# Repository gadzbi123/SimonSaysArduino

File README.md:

# SimonSaysArduino
Simple Arduino project

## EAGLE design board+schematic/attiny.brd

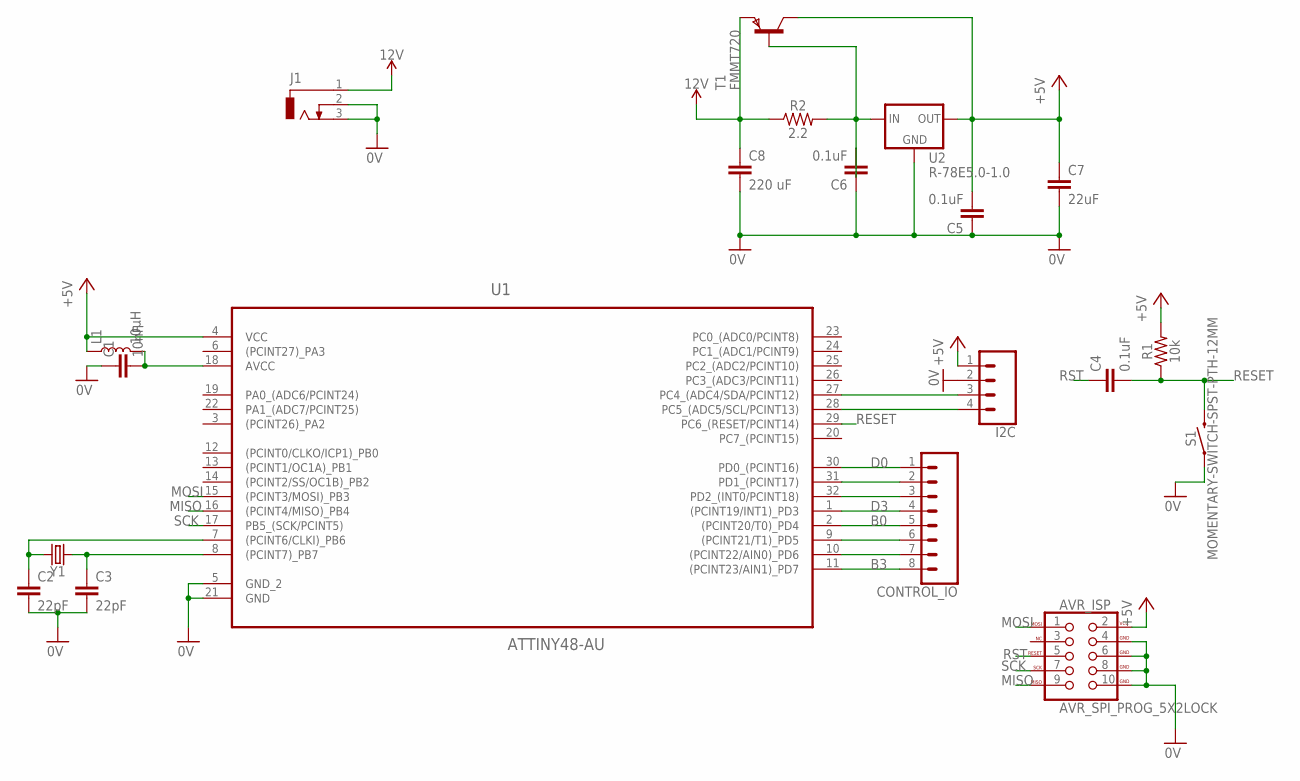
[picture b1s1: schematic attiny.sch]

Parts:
AVR_ISP: AVR_SPI_PROG_5X2LOCK; 2X5-SHROUDED_LOCK
C1: 10nF; CAP-PTH-10MM
C2, C3: 22pF; 0603
C4, C5, C6: 0.1uF; CAP-PTH-SMALL-KIT
C7: 22uF; 0805
C8: 220 uF; C7.5B5
CONTROL_IO: CONN_08"; 1X08
I2C: CONN_04PTH; 1X04
J1: DCJ0303
L1: 10μH; 0805
R1: 10k; AXIAL-0.3
R2: 2.2; 0603
S1: MOMENTARY-SWITCH-SPST-PTH-12MM; TACTILE_SWITCH_PTH_12MM
T1: FMMT720; SOT-23
U1: ATTINY48-AU; QFP80P900X900X120-32N
U2: R-78E5.0-1.0; DC-DC_CONVERTER_78XX
Y1: CRYSTALPTH-2X6; CRYSTAL-PTH-2X6-CYL

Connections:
0V: AVR_ISP.4 (GND), AVR_ISP.6 (GND), AVR_ISP.8 (GND), AVR_ISP.10 (GND), C1.1, C2.2, C3.2, C5.1, C6.1, C7.2, C8.2, I2C.2, J1.2, J1.3, S1.1, U1.5 (GND_2), U1.21 (GND), U2.GND
12V: C8.1, J1.1, R2.1, T1.2 (E)
+5V: AVR_ISP.2 (VCC), C5.2, C7.1, I2C.1, L1.1, R1.P$2 (2), T1.1 (C), U1.4 (VCC), U2.VOUT (OUT)
B0: CONTROL_IO.5, U1.2 ((PCINT20/T0)_PD4)
B3: CONTROL_IO.8, U1.11 ((PCINT23/AIN1)_PD7)
D0: CONTROL_IO.1, U1.30 (PD0_(PCINT16))
D3: CONTROL_IO.4, U1.1 ((PCINT19/INT1)_PD3)
MISO: AVR_ISP.9 (MISO), U1.16 ((PCINT4/MISO)_PB4)
MOSI: AVR_ISP.1 (MOSI), U1.15 ((PCINT3/MOSI)_PB3)
unnamed: C1.2, L1.2, U1.18 (AVCC)
unnamed: I2C.3, U1.27 (PC4_(ADC4/SDA/PCINT12))
unnamed: I2C.4, U1.28 (PC5_(ADC5/SCL/PCINT13))
unnamed: C2.1, U1.7 ((PCINT6/CLKI)_PB6), Y1.2
unnamed: C3.1, U1.8 ((PCINT7)_PB7), Y1.1
unnamed: C6.2, R2.2, T1.3 (B), U2.VIN (IN)
unnamed: CONTROL_IO.2, U1.31 (PD1_(PCINT17))
unnamed: CONTROL_IO.3, U1.32 (PD2_(INT0/PCINT18))
unnamed: CONTROL_IO.6, U1.9 ((PCINT21/T1)_PD5)
unnamed: CONTROL_IO.7, U1.10 ((PCINT22/AIN0)_PD6)
RESET: C4.2, R1.P$1 (1), S1.3 (2), U1.29 (PC6_(RESET/PCINT14))
RST: AVR_ISP.5 (RESET), C4.1
SCK: AVR_ISP.7 (SCK), U1.17 (PB5_(SCK/PCINT5))

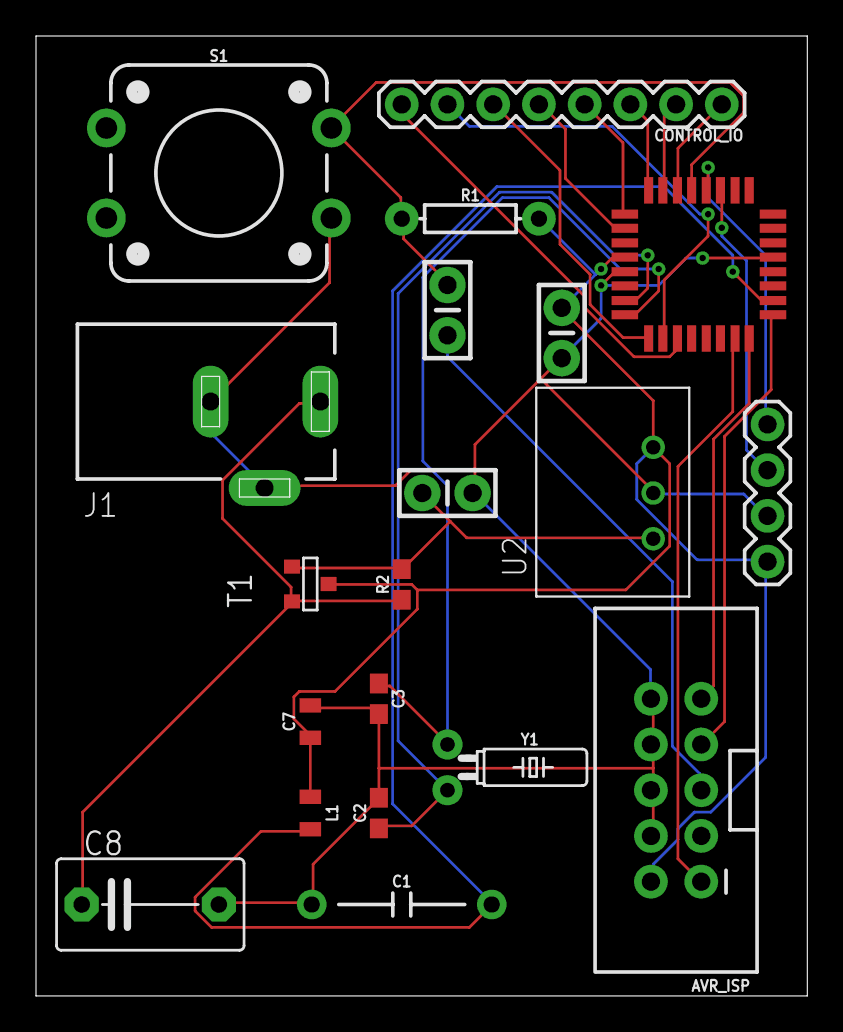
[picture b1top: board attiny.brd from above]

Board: 2 copper layers, 42.9 x 53.3 mm, 20 parts (0 on the bottom side), 22 nets.

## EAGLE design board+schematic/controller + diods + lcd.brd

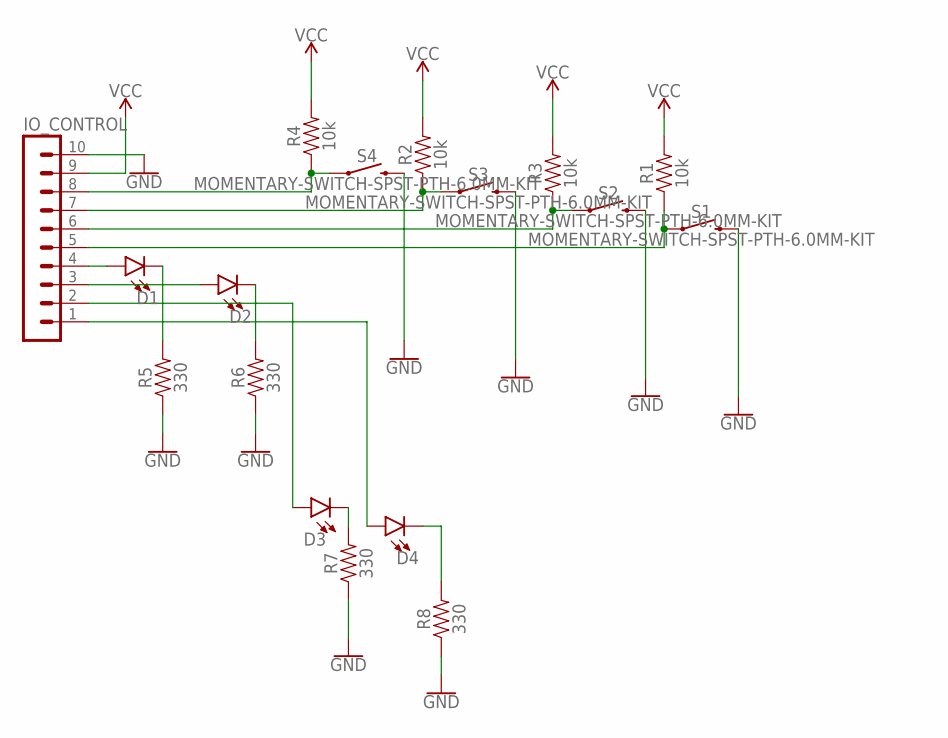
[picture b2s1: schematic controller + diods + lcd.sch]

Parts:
D1, D2, D3, D4: LED10MM; LED_10MM
IO_CONTROL: MA10-1
R1, R2, R3, R4: 10k; AXIAL-0.3-KIT
R5, R6, R7, R8: 330; AXIAL-0.3
S1, S2, S3, S4: MOMENTARY-SWITCH-SPST-PTH-6.0MM-KIT; TACTILE_SWITCH_PTH_6.0MM_KIT

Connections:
GND: IO_CONTROL.10, R5.P$1 (1), R6.P$1 (1), R7.P$1 (1), R8.P$1 (1), S1.3 (2), S2.3 (2), S3.3 (2), S4.3 (2)
unnamed: IO_CONTROL.6, R3.P$1 (1), S2.1
unnamed: IO_CONTROL.7, R2.P$1 (1), S3.1
unnamed: IO_CONTROL.8, R4.P$1 (1), S4.1
unnamed: D1.A, IO_CONTROL.4
unnamed: D1.C, R5.P$2 (2)
unnamed: D2.A, IO_CONTROL.3
unnamed: D2.C, R6.P$2 (2)
unnamed: D3.A, IO_CONTROL.2
unnamed: D3.C, R7.P$2 (2)
unnamed: D4.A, IO_CONTROL.1
unnamed: D4.C, R8.P$2 (2)
unnamed: IO_CONTROL.5, R1.P$1 (1), S1.1
VCC: IO_CONTROL.9, R1.P$2 (2), R2.P$2 (2), R3.P$2 (2), R4.P$2 (2)

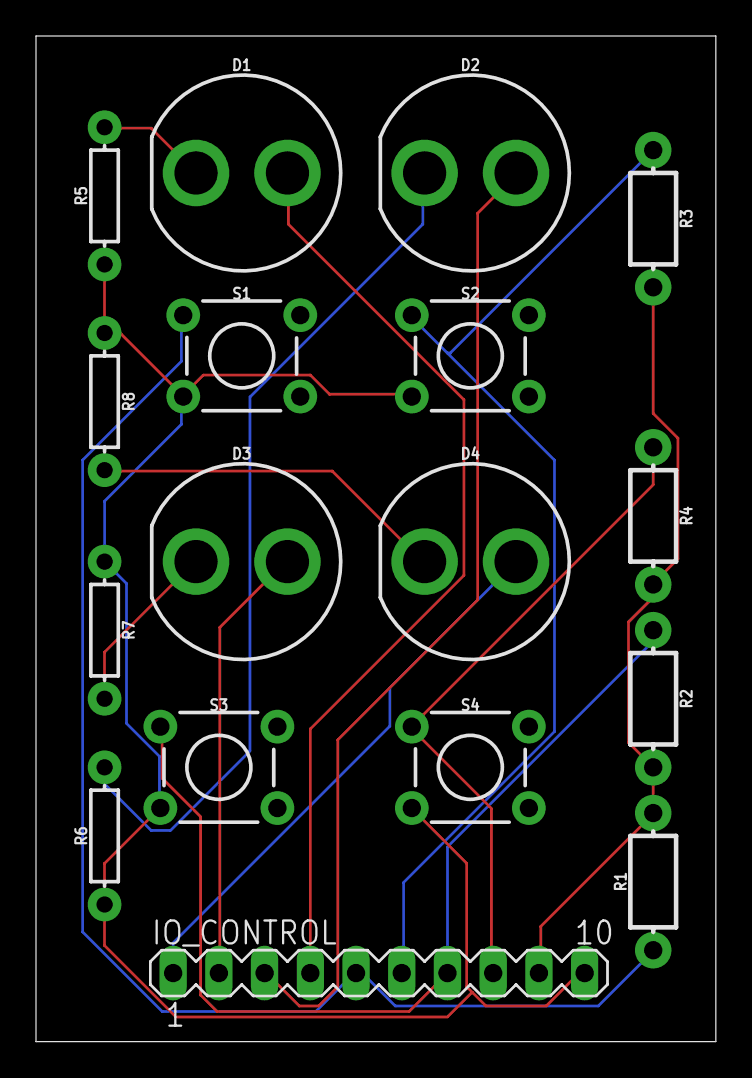
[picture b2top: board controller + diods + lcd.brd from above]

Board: 2 copper layers, 37.8 x 55.9 mm, 17 parts (0 on the bottom side), 14 nets.

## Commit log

2024-04-27 inital commit
2024-04-27 added movie

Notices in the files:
parts and their libraries:
SparkFun-Connectors: Licensing: Creative Commons ShareAlike 4.0 International - https://creativecommons.org/licenses/by-sa/4.0
